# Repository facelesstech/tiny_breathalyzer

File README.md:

# tiny_breathalyzer
tiny_breathalyzer

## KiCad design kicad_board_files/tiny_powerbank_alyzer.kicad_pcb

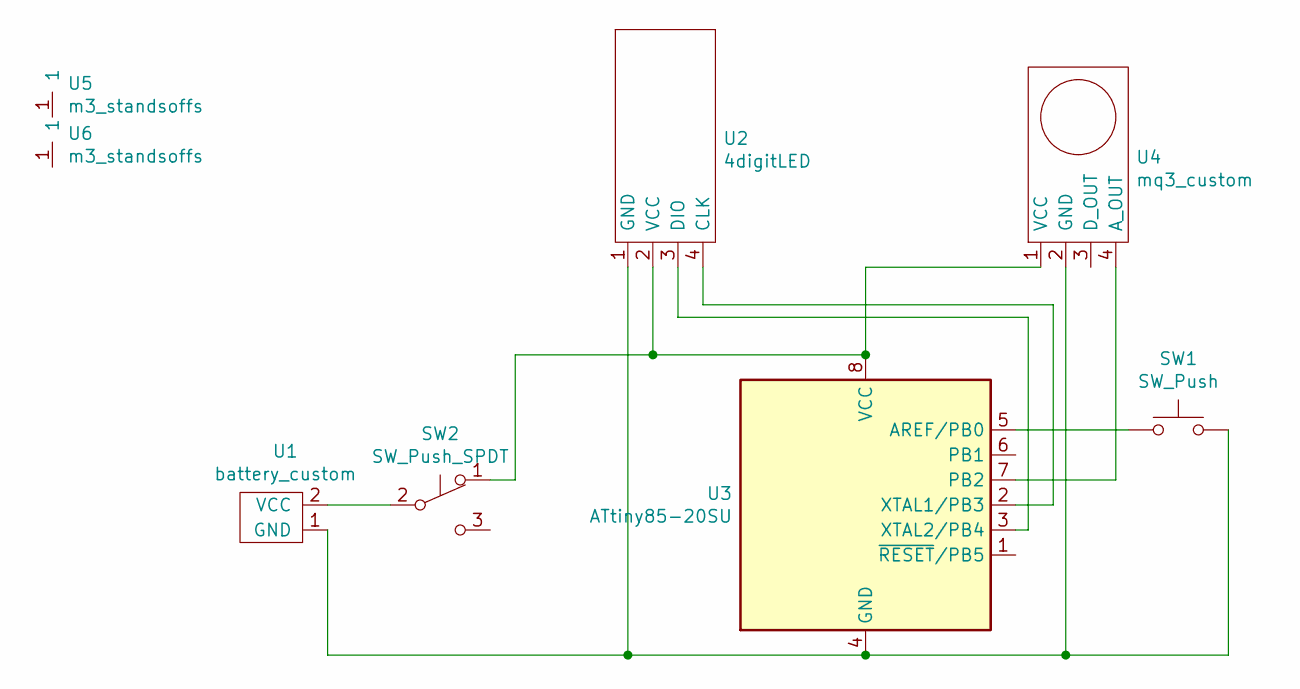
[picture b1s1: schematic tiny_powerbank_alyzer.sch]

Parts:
SW1: SW_Push; SMD_2pin_button_custom
SW2: SW_Push_SPDT; latch_switch_7x7
U1: battery_custom; jst_2pin_custom
U2: 4digitLED; 4digitLED_custom
U3: ATtiny85-20SU; SOIJ-8_5.3x5.3mm_P1.27mm
U4: mq3_custom; mq-3_custom_blue
U5, U6: m3_standsoffs; m3_hole_custom

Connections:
unnamed: SW1.1, U3.5 (AREF/PB0)
unnamed: SW1.2, U1.1 (GND), U2.1 (GND), U3.4 (GND), U4.2 (GND)
unnamed: SW2.1 (A), U2.2 (VCC), U3.8 (VCC), U4.1 (VCC)
unnamed: SW2.2 (B), U1.2 (VCC)
unnamed: U2.3 (DIO), U3.3 (XTAL2/PB4)
unnamed: U2.4 (CLK), U3.2 (XTAL1/PB3)
unnamed: U3.7 (PB2), U4.4 (A_OUT)

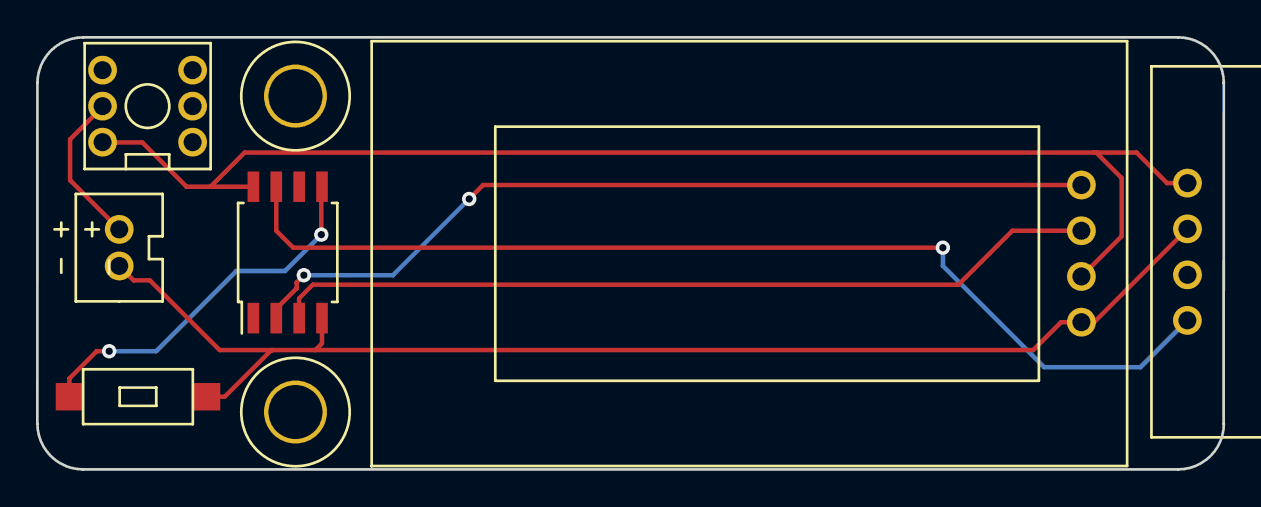
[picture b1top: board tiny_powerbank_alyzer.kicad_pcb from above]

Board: 2 copper layers, 65.9 x 24.0 mm, 8 parts (0 on the bottom side), 7 nets.

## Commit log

2020-02-27 kicad board files
2020-02-27 arduino board files
2020-03-21 changed start value and start up time to 1 and half mins
2020-03-21 3d printing files
